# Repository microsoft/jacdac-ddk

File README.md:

> [!IMPORTANT]
> This repository has moved to https://github.com/jacdac/jacdac-ddk 

# Jacdac Device Development Kit (DDK) Reference Materials

## Introduction

This repository contains reference materials for creators of [Jacdac](https://aka.ms/jacdac) devices. More specifically, it has technical drawings, part libraries and device designs (schematics and layout files). In conjunction with the [Jacdac device design documentation](https://microsoft.github.io/jacdac-docs/ddk/) and our [Jacdac firmware repositories](https://microsoft.github.io/jacdac-docs/ddk/firmware/), these materials form the Jacdac device design kit (DDK). The DDK contains everything necessary to design and manufacture [Jacdac devices](https://microsoft.github.io/jacdac-docs/devices/).

Please also refer to discussions at https://github.com/microsoft/jacdac/discussions and note that issues are tracked on https://github.com/microsoft/jacdac/issues.

## Repository structure

-   `/connector`: specification of the Jacdac PCB connector, cable connector and cable assemblies;
-   `/electronics`: reference materials and implementations of different types of device in the form of schematics, layouts and parts libraries for various electronics CAD packages;
-   `/enclosures`: files relating to enclosures for Jacdac modules and devices; and
-   `/graphics`: image files that might be useful for device design, packaging and/or marketing materials.

Note that the contents of any files under a `deprecated_form_factor` or `explorations` folder are provided for interest only, these should not be considered reference material relating to the Jacdac standard.

## Contributing to Jacdac

This project welcomes contributions and suggestions. Most contributions require you to agree to a
Contributor License Agreement (CLA) declaring that you have the right to, and actually do, grant us
the rights to use your contribution. For details, visit https://cla.opensource.microsoft.com.

When you submit a pull request, a CLA bot will automatically determine whether you need to provide
a CLA and decorate the PR appropriately (e.g., status check, comment). Simply follow the instructions
provided by the bot. You will only need to do this once across all repos using our CLA.

This project has adopted the [Microsoft Open Source Code of Conduct](https://opensource.microsoft.com/codeofconduct/).
For more information see the [Code of Conduct FAQ](https://opensource.microsoft.com/codeofconduct/faq/) or
contact [opencode@microsoft.com](mailto:opencode@microsoft.com) with any additional questions or comments.

## Legal Notices

Microsoft and any contributors grant you a license to the Microsoft documentation and other content
in this repository under the [Creative Commons Attribution 4.0 International Public License](https://creativecommons.org/licenses/by/4.0/legalcode),
see the [LICENSE](LICENSE) file, and grant you a license to any code in the repository under the [MIT License](https://opensource.org/licenses/MIT), see the
[LICENSE-CODE](LICENSE-CODE) file, and grant you a license to any hardware designs in the repository under the [CERN Open License v2](https://opensource.org/license/cern-ohl-p), see the [LICENSE-HARDWARE](LICENSE-HARDWARE) file.

Use of this open hardware project, as well as any physical hardware created using it, carries risks of malfunction or failure. It is not subject to the same testing and quality control as designs created for products to be put into commerce and may not be suitable for mission-critical, high-risk applications, or other uses where failure could result in personal injury, death, property damage, other harm or loss including but not limited to data loss or corruption. By using this project or any hardware created using it, you assume all risks and agree to not hold its creators or distributors responsible for any damages or losses resulting from that use.

Microsoft, Windows, Microsoft Azure and/or other Microsoft products and services referenced in the documentation
may be either trademarks or registered trademarks of Microsoft in the United States and/or other countries.
The licenses for this project do not grant you rights to use any Microsoft names, logos, or trademarks.
Microsoft's general trademark guidelines can be found at http://go.microsoft.com/fwlink/?LinkID=254653.

Privacy information can be found at https://privacy.microsoft.com/en-us/

Microsoft and any contributors reserve all other rights, whether under their respective copyrights, patents,
or trademarks, whether by implication, estoppel or otherwise.

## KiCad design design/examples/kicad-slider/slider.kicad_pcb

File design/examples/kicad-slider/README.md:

# Example Slider Module for Jacdac, in KiCad

This is an example / reference Jacdac module for a slider potentiometer built in [KiCad](https://www.kicad.org/), an open-source PCB design suite.

| Schematic | Board |
| --- | --- |
|  | Front side <br />  <br /><br /> Back side <br />  |

## Structure overview

This KiCad project uses local (per-project, relative path) references to the Jacdac symbol and footprint libraries that are included in this repository.
This also includes a project-specific `slider.pretty` footprint library containing the module QR code, as generated by the [Jacdac Silk QR Code generator](https://microsoft.github.io/jacdac-docs/tools/qr-silk/), and consistent with its entry in the [device map CSV](https://github.com/microsoft/jacdac/blob/main/devices/microsoft/research/qr-url-device-map.csv).

Fabrication data (gerbers, pick-and-place) is included in the `fab-1.1` folder.

## Fabrication notes for JLC

We fabricated our prototype run for this board with JLCPCB, which offers low-volume board fabrication and single-sided assembly services.
Below are notes for how we generated fabrication data.

### Gerbers
Gerbers can be generated with the typical KiCad flow.

### Part numbers
In the schematic, we added a `LCSC` field to all components, containing the JLCPCB part numbers.
To generate the pick-and-place parts: in the schematic editor, go to Tools menu > Generate Bill of Materials..., run bom2grouped_csv, which produces a `slider.csv` in the project directory.
This should have an LCSC column with the JLC part numbers.

Rename columns as follows:
- `Reference` -> `Designators`
- `LCSC` -> `LCSC Part #`
- `Value` -> `Comment`
- Other columns can be left as-is

*Note: this was built against an older JLCPCB sample BoM file which used the column name `LCSC Part #`, instead of the `JLCPCB Part #` used in a newer sample BoM.*

### Positions
In the layout editor, go to File menu > Fabrication Outputs > Footprint Position (.pos) File...
Since JLC does one layer only, select "Separate files for front and back".
This creates a `slider-bottom-pos.csv` (and top file that can be discarded) in the output directory.

Rename columns as follows:
- `Ref` -> `Designator`
- `PosX` -> `Mid X`
- `PosY` -> `Mid Y`
- `Side` -> `Layer`
- Other columns can be left as-is

Optionally, correct rotations on parts.
While we've sent in fabrication data with obviously wrong rotations (eg, TSSOP-20 oriented 90 degree off) and didn't get obviously wrong PCBs back, you can correct the rotations using a spreadsheet tool like Excel:
- Rename `Rot` to something different, eg `KiCadRot`.
- Add a `RotCorrection` column or something, to be manually set for each part. Positive rotation is clockwise (unmirrored view, at least on the bottom layer).
- Add a `Rotation` column, set to the formula of the KiCadRot cell plus the RotCorrection cell. **This is the column containing the actual fabrication data.**

### Ordering Notes
In the PCB options, choose:
- Upload gerbers
- PCB Qty: as desired
- Surface Finish: ENIG-RoHS
- Gold Fingers: Yes
- 45 finger chamfered: No (ideally yes, but the board is too small)
- The defaults for the rest are fine

In the SMT Assembly options, choose:
- Assembly bottom side (the side with the QR code)
- Tooling holes: Added by JLCPCB
- Click "confirm"
- Add BOM File -> upload the `slider.csv` file (schematic BoM)
- Add CPL file -> upload the `slider-bottom-pos.csv` file (layout footprint position)
- Click "next"
- Review the component table
- Click "next"
- Review the placed preview, and fix footprint data as necessary (red dot indicates pin 1?)
  - If you need to go back, there is a not-at-all-obvious grey "< Go back" link at the bottom left of the page
- Review unselected parts: these are parts that will not be placed and should only be top-layer or other items to be manually soldered, card edge connectors, and mounting holes
- Click "save to cart"

Stencils:
- From the shopping cart, "Add new item"
- At the top, select the SMT-Stencil tab
- Upload gerbers, same as the PCB
- Stencil Side: Top & Bottom(On Separate Stencil)
- Stencil Qty: 2 (default)
- Fiducials: Etched Through
- Click "save to cart"

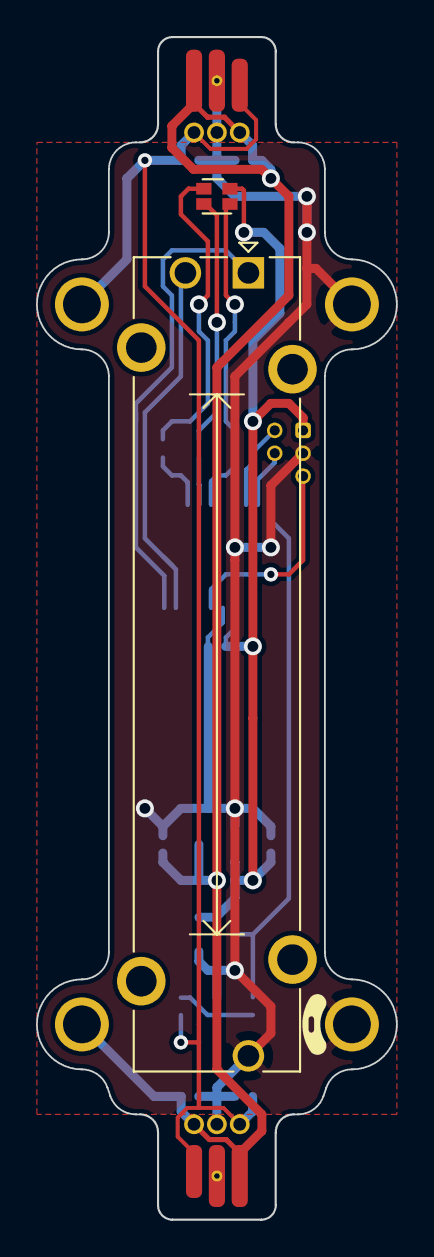
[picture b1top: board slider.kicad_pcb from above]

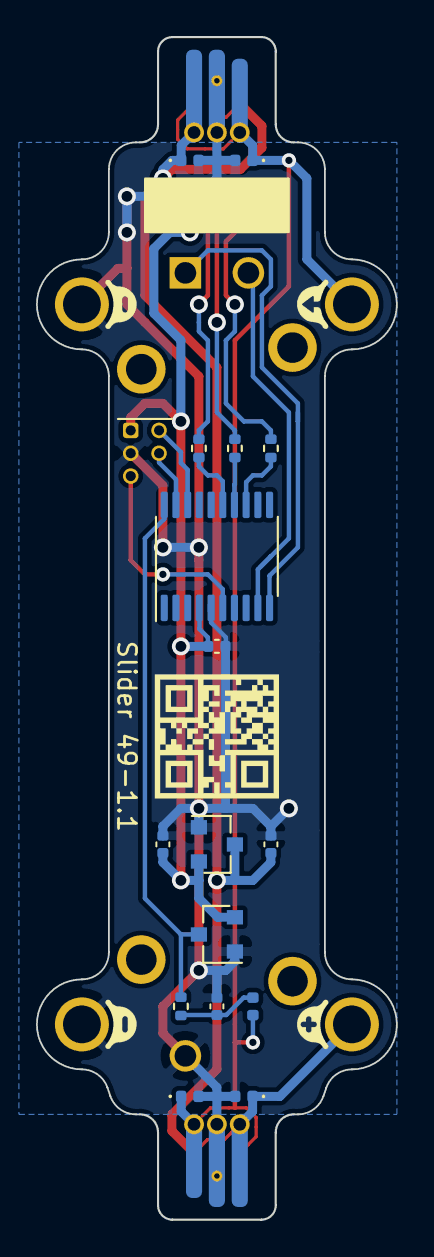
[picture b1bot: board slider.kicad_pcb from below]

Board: 2 copper layers, 20.0 x 65.7 mm, 25 parts (19 on the bottom side), 17 nets.

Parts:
C1: 33pF; C_0402_1005Metric
C2: 1uF, 10V; C_0402_1005Metric
C3, C5: 1uF; C_0402_1005Metric
D1: BAT54S; SOT-23
D2, D3, D5, D6: RCLAMP0521P-N; D_0402_1005Metric
D4: 0606 ARGB; LED_LiteOn_LTST-C19HE1WT
FB1: 1kR @ 100MHz; L_0402_1005Metric
J1, J3: Conn_Jacdac_CardEdge; JD-PEC-01_Prerouted
J2: Conn_HackConnect; HackConnect_P1.27mm
MH1: MountingHole_Pad; JD_MountingHole_Pin1
MH2: MountingHole_Pad; JD_MountingHole_Ground
MH3: MountingHole_Pad; JD_MountingHole_Data
MH4: MountingHole_Pad; JD_MountingHole_Power
R1: 220R, 1%; R_0402_1005Metric
R4: 150R; R_0402_1005Metric
R5, R6: 33R; R_0402_1005Metric
RV1: 10kR; Potentiometer_Bourns_PTA3043_Single_Slide
U1: XC6206P332MR; SOT-23
U2: STM32G031FxPx; TSSOP-20_4.4x6.5mm_P0.65mm

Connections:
+3V3: C3.1, C5.1, D1.2, D4.1, J2.1, U1.2, U2.4
/JD_DATA: D3.1, D6.1, FB1.2, J1.1, J3.1, MH3.1
/JD_DATA_MCU: D1.3, R1.1, U2.20
/JD_RGB_B: R6.1, U2.13
/JD_RGB_G: R5.1, U2.14
/JD_RGB_R: R4.1, U2.15
/POT_OUT: RV1.2, U2.9
/POT_VDD: RV1.1, U2.10
/SWCLK: J2.4, U2.19
/SWDIO: J2.2, U2.18
/nRESET: J2.5, U2.6
GND: C1.2, C2.2, C3.2, C5.2, D1.1, D2.2, D3.2, D5.2, D6.2, J1.2, J2.3, J3.2, MH1.1, MH2.1, RV1.3, U1.1, U2.5
JD_PWR: C2.1, D2.1, D5.1, J1.3, J3.3, MH4.1, U1.3
unnamed: C1.1, FB1.1, R1.2
unnamed: D4.2, R4.2
unnamed: D4.3, R5.2
unnamed: D4.4, R6.2

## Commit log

2020-12-16 Initial LICENSE commit
2020-12-16 Initial CODE_OF_CONDUCT.md commit
2020-12-16 Initial LICENSE-CODE commit
2020-12-16 Initial README.md commit
2020-12-16 Initial SECURITY.md commit
2020-12-16 adding connector folder
2020-12-16 Update README.md
    Adding title
2020-12-16 added PCB edge connector drawing
2020-12-16 using underscores in pdf names
2020-12-16 add connector
2020-12-16 updated link
2020-12-16 link to folder
2020-12-16 add link to pdf
2020-12-16 link to jacdac
2020-12-16 Link firmware repos
2020-12-16 bring over text from word doc
2020-12-16 add link to devices
2020-12-16 components
2020-12-16 add more structure
2020-12-17 Rename and link connector PDF
2020-12-17 typos corrected
2021-02-12 add a page for module submission
2021-02-16 Explain about pin order
2021-02-16 resize image
2021-02-16 resizing doesn't work
2021-02-16 another attempt at sizing
2021-02-16 simpler path for image
2021-02-23 rename JACDAC to Jacdac
2021-04-06 MDK -> DDK
2021-04-06 header
2021-04-06 jacdac-ts -> jacdac-docs
2021-04-06 remove extra
2021-04-06 remove module
2021-04-06 typos
2021-04-06 three features, just three!
2021-04-06 typo fixed
2021-04-07 host -> server
2021-04-07 small update
2021-05-03 updated README.md
    Broadened scope to include power supplies and Jacdaptors in addition to modules and brains.
    Highlighted the existence of dedicated vs. integrated brains.
    Re-structured to improve flow.
    Refined text throughout.
2021-05-03 Update README.md
    Added motivation that's consistent with other Jacdac docs.
2021-05-03 Update README.md
    Initial draft underway.
2021-05-03 Update README.md
    Continuing with first draft.
2021-05-07 Add firmware page and link it
2021-05-24 JACDAC -> Jacdac
2021-06-30 test commit from VS Code
2021-07-02 Revised hardware design guidelines
2021-07-15 updated PCB edge connecter dwg, refined text
2021-07-23 more edits
2021-07-26 add reference design and notes
2021-07-26 remote outdated descs
2021-07-26 cleanup footprint reradme
2021-07-26 pictures
2021-07-26 cleanup + schematic
2021-07-26 lol ouch
2021-08-06 partner preview message
2021-08-13 Rename JD-PEC-01 to JC-PEC-02
2021-08-13 update stragglers
2021-08-13 Update JLCPCB Part #
2021-08-13 words
2021-08-13 grammar
2021-08-13 words, again
2021-09-10 don't point to beta editor
2021-09-11 Adding EAGLE Jacdac footrpitns and design blocks
2021-09-11 syntax
2021-12-01 reorg design folders
2021-12-01 rename library => libraries; add subfolders to altium
2021-12-01 update slider file references
2021-12-02 add Jacdac.IntLib under altium
2021-12-02 updates to docs for public release
2021-12-02 adding link to the QR code generator for devices
2021-12-02 remove duplicated markdown
2021-12-02 typo
2021-12-02 more cleanup
2021-12-03 updated folder name
2021-12-03 Add Rotary and Temp+Humidity reference designs
2021-12-03 Add micro:bit Jacdapter reference design
2021-12-03 Add RGBLedRing reference design
2021-12-03 Add G0 Button reference design
2021-12-03 removing extra electronics/readme file
2021-12-20 Add accelerometer reference design
2021-12-20 Add generic RGB LED strip reference design
2021-12-20 Add padauk light level sensor reference design
2021-12-21 Add padauk analog joystick reference design
2021-12-21 Remove status report text files
2022-01-10 Add Access Switch Input 1.4
2022-01-11 link to jacdac issues
2022-02-07 updated qr code generator link
2022-02-17 fix links
2022-05-26 move old designs to deprecated_form_factor
2022-05-27 adding graphics
2022-06-06 ec30 pdf
2022-06-12 Add MSR Gyro board reference design
2022-06-13 Update README.md
    add link to EC30 spec
2022-06-13 rotate LSM6D to match JLC spec
2022-06-13 add printout of schematics
2022-06-13 ignore generated eagle files
2022-06-13 add generated files
2022-06-14 additions to DDK
2022-06-14 updating reference CAD files
2022-06-15 renamed folder
2022-06-15 fixed typos
2022-06-15 adding altium reference designs
2022-06-16 improved introduction
2022-06-16 updated suggested components
2022-06-16 added current limiters
2022-06-16 added component details
2022-06-16 edits to schottky diode table
2022-06-17 remove old files
2022-06-17 use aka.ms links in readme
2022-06-17 updated altium edge connector reference design
2022-06-17 added altium module reference designs
2022-06-21 fix connector size in EAGLE library
2022-06-21 update size of the jacdac connector in EAGLE design
2022-06-21 add generated gerber and BOM/PNP
2022-06-26 added ref schematics, cable connector STEP, diode
2022-06-27 edit to readme
2022-07-25 adding Jacdac cable extender design files
2022-08-15 added push buttons, USB C connectors, crystals
2023-09-14 adding RP2040 brain
2023-10-13 adding miscellaneous design files
2025-03-19 add CERN
2025-03-19 renaming
2025-08-13 move to jacdac org
